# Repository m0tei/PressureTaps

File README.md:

# Pressure Taps

A 16-channel aero pressure tap board for ArtTU. It reads 16 pressure ports and one reference port over SPI and sends the data out on CAN. The sensors sit in sealed chambers, with a glued cover on top and a tube block underneath.

| | |
|---|---|
| Board size | 86 × 50 mm, 1.6 mm thick, 4 layers |
| Layers | Top, GND plane, GND+PWR (3V3) plane, bottom |
| MCU | STM32G483RET6 |
| Sensors | 17 × LPS27HHW (16 taps and 1 reference) on one SPI bus |
| Supply | 12 V in, 5 V and 3.3 V on board |
| Bus | CAN through a TJA1441, with switchable termination on P3 and P4 |
| Connector | TE Ampseal 2489696-1, 8 pin |
| Design tool | KiCad 10 |

> **Status:** this design passes KiCad's electrical and layout checks. This repository has no test results from a built board.

## The board

**Top side:** sensors on the left, MCU in the middle, CAN below it and the two regulators stacked in the top right corner. SWD, reset and BOOT0 are in a row along the top edge.

**Bottom side:** tube port labels and the Ampseal connector.

The sensor grid is centred top to bottom: 7.0 mm from the grid to each long edge. The clamp holes H5 to H8 are centred on the same line.

## Schematic

The full schematic is in [docs/schematic.pdf](docs/schematic.pdf). It has five sheets:

| Sheet | Contents |
|---|---|
| MCU | U1, BOOT0, reset, clock, SPI series resistors, MCU power and the VDDA regulator |
| Communication | CAN transceiver, choke, termination and ESD protection |
| Connectors | SWD header, Ampseal connector, mounting holes and fiducials |
| Power | 5 V and 3.3 V regulators, power flags |
| Sensors | The 17 pressure sensors and bulk capacitor |

The schematic style and part choices follow the ArtTU Gateway boards. Footprints named `GW_*` use pads measured from CAN_Gateway RevA.

## Ampseal pinout

| Pin | Signal |
|---|---|
| 1 to 4 | Not connected |
| 5 | GND |
| 6 | 12 V |
| 7 | CAN_N |
| 8 | CAN_P |

## Enclosure

The press-fit enclosure is in [mechanical/press_fit](mechanical/press_fit). It has four printed parts: case top, case bottom, sensor cover and tube block. STEP and STL files are in that folder.

To rebuild the parts, run this from the repository root:

```bash
uv run --no-project --python 3.12 --with cadquery==2.8.0 python -I mechanical/press_fit/enclosure.py mechanical/press_fit
```

The board size and hole positions in `enclosure.py` must match the PCB. Change both together.

## Bill of materials

The BOM is in [PressureTaps_BOM.csv](PressureTaps_BOM.csv). Parts shared with the Gateway use the same part numbers, manufacturers and suppliers.

## Open items

- R20 and R21 (33 Ω, SPI series resistors) have no part number yet.
- The P2, P3 and P4 pin headers do not fit under the case lid.
- D1 uses a standard SOT-323 footprint. The Gateway footprint for the same part has wider pad spacing, so it was not copied. Check it against the datasheet drawing.

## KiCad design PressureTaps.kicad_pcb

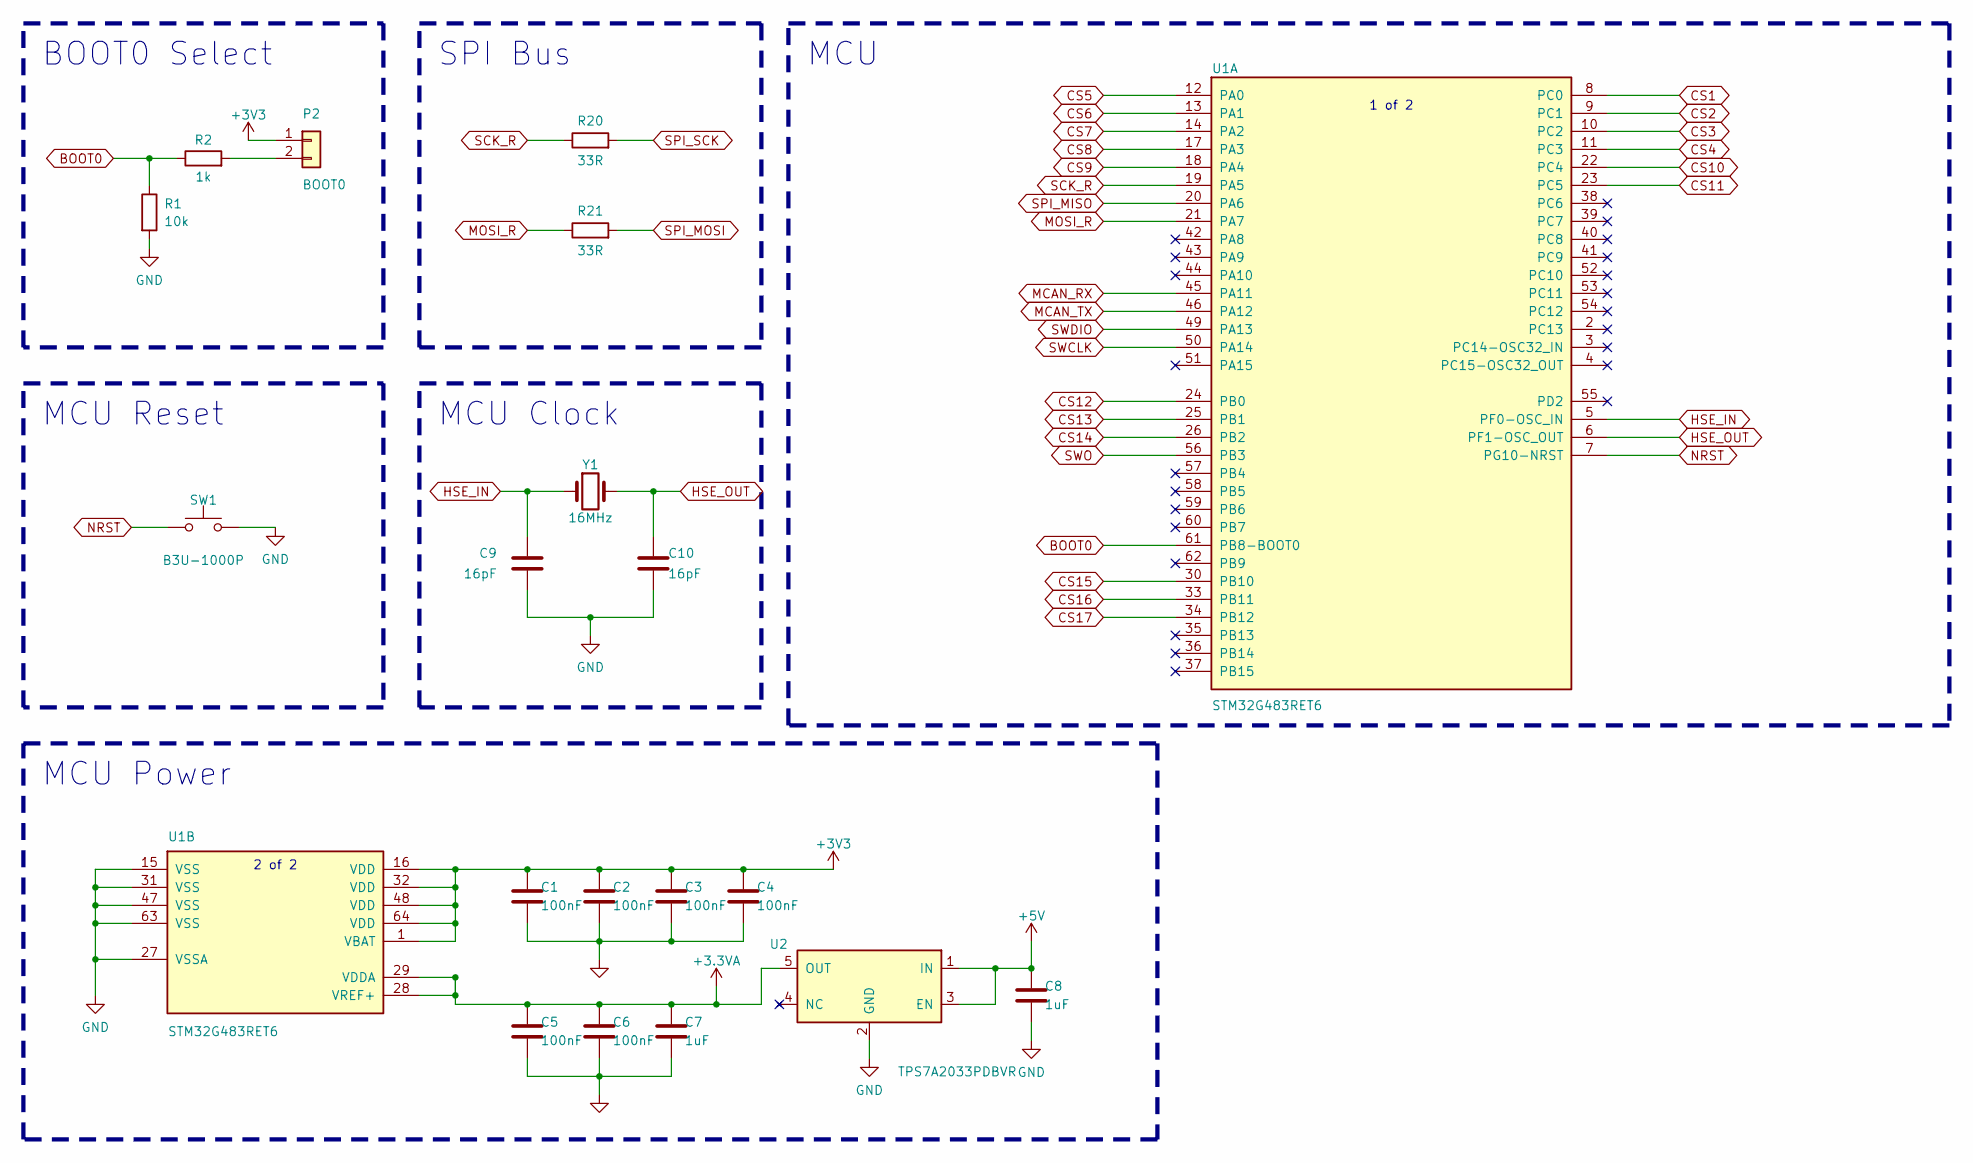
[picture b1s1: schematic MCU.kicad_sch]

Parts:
C1, C2, C3, C4, C5, C6: 100nF; GW_C1; MPN CC0603JRX7R9BB104
C7, C8: 1uF; GW_C7; MPN CC0603KRX5R8BB105
C9, C10: 16pF; GW_C9; MPN C0603C160J5HACTU
P2: BOOT0; GW_P2; MPN 62000211121
R1: 10k; GW_R1; MPN AF0603FR-0710KL
R2: 1k; GW_R2; MPN ERJ-6ENF1001V
R20, R21: 33R; GW_R1
SW1: B3U-1000P; SW_SPST_B3U-1000P; MPN B3U-1000P
U1: STM32G483RET6; GW_U1; MPN STM32G483RET6
U2: TPS7A2033PDBVR; GW_U2; MPN TPS7A2033PDBVR
Y1: 16MHz; GW_Y1; MPN ABM3-16.000MHZ-D2Y-T

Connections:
+3.3VA: C5.1, C6.1, C7.1, U1.28 (VREF+), U1.29 (VDDA), U2.5 (OUT)
+3V3: C1.1, C2.1, C3.1, C4.1, P2.1, U1.1 (VBAT), U1.16 (VDD), U1.32 (VDD), U1.48 (VDD), U1.64 (VDD); also elsewhere on the board
+5V: C8.1, U2.1 (IN), U2.3 (EN); also elsewhere on the board
BOOT0: R1.1, R2.1, U1.61 (PB8-BOOT0)
CS1: U1.8 (PC0); also elsewhere on the board
CS2: U1.9 (PC1); also elsewhere on the board
CS3: U1.10 (PC2); also elsewhere on the board
CS4: U1.11 (PC3); also elsewhere on the board
CS5: U1.12 (PA0); also elsewhere on the board
CS6: U1.13 (PA1); also elsewhere on the board
CS7: U1.14 (PA2); also elsewhere on the board
CS8: U1.17 (PA3); also elsewhere on the board
CS9: U1.18 (PA4); also elsewhere on the board
CS10: U1.22 (PC4); also elsewhere on the board
CS11: U1.23 (PC5); also elsewhere on the board
CS12: U1.24 (PB0); also elsewhere on the board
CS13: U1.25 (PB1); also elsewhere on the board
CS14: U1.26 (PB2); also elsewhere on the board
CS15: U1.30 (PB10); also elsewhere on the board
CS16: U1.33 (PB11); also elsewhere on the board
CS17: U1.34 (PB12); also elsewhere on the board
GND: C1.2, C2.2, C3.2, C4.2, C5.2, C6.2, C7.2, C8.2, C9.2, C10.2, R1.2, SW1.2, U1.15 (VSS), U1.27 (VSSA), U1.31 (VSS), U1.47 (VSS), U1.63 (VSS), U2.2 (GND); also elsewhere on the board
HSE_IN: C9.1, U1.5 (PF0-OSC_IN), Y1.1
HSE_OUT: C10.1, U1.6 (PF1-OSC_OUT), Y1.2
MCAN_RX: U1.45 (PA11); also elsewhere on the board
MCAN_TX: U1.46 (PA12); also elsewhere on the board
MOSI_R: R21.1, U1.21 (PA7)
NRST: SW1.1, U1.7 (PG10-NRST); also elsewhere on the board
unnamed: P2.2, R2.2
SCK_R: R20.1, U1.19 (PA5)
SPI_MISO: U1.20 (PA6); also elsewhere on the board
SPI_MOSI: R21.2; also elsewhere on the board
SPI_SCK: R20.2; also elsewhere on the board
SWCLK: U1.50 (PA14); also elsewhere on the board
SWDIO: U1.49 (PA13); also elsewhere on the board
SWO: U1.56 (PB3); also elsewhere on the board

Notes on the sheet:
BOOT0 Select
SPI Bus
MCU Reset
MCU Clock
MCU
1 of 2
MCU Power
2 of 2

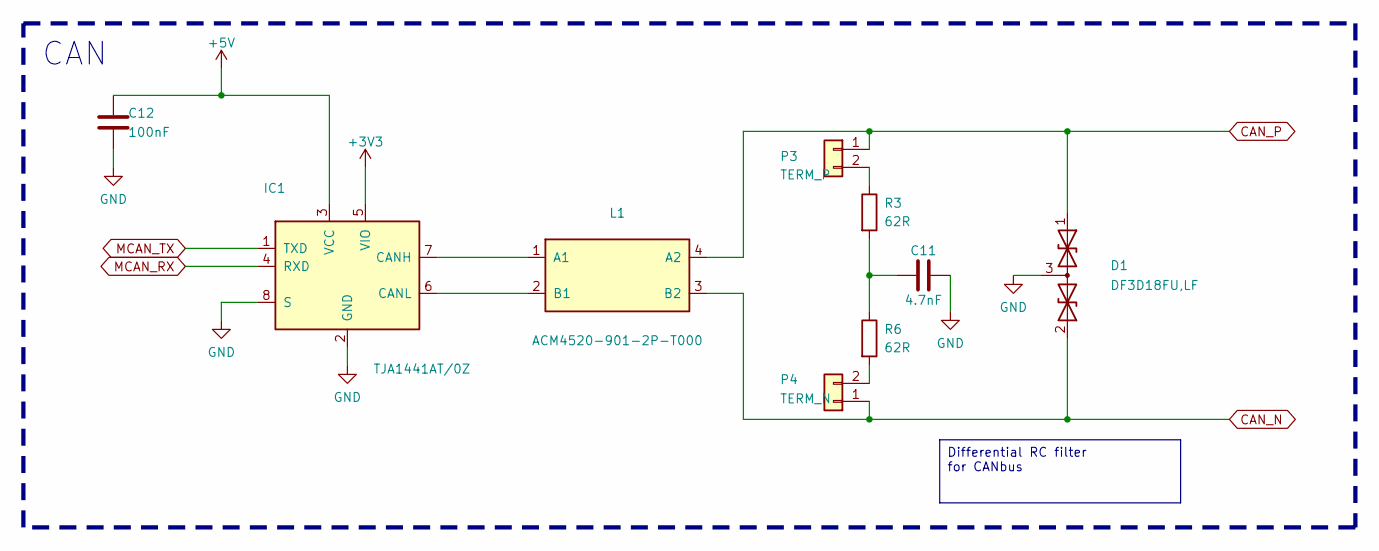
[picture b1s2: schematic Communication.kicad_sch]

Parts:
C11: 4.7nF; GW_C11; MPN C0603C472J5RACTU
C12: 100nF; GW_C12; MPN CC0603JRX7R9BB104
D1: DF3D18FU,LF; SOT-323_SC-70; MPN DF3D18FU,LF
IC1: TJA1441AT/0Z; GW_IC1; MPN TJA1441AT/0Z
L1: ACM4520-901-2P-T000; L_ACM4520; MPN ACM4520-901-2P-T000
P3: TERM_P; GW_P2; MPN 62000211121
P4: TERM_N; GW_P2; MPN 62000211121
R3, R6: 62R; GW_R3; MPN ERA3AEB620V

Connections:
+3V3: IC1.5 (VIO); also elsewhere on the board
+5V: C12.1, IC1.3 (VCC); also elsewhere on the board
CAN_N: D1.2 (A2), L1.3 (B2), P4.1; also elsewhere on the board
CAN_P: D1.1 (A1), L1.4 (A2), P3.1; also elsewhere on the board
GND: C11.2, C12.2, D1.3 (common), IC1.2 (GND), IC1.8 (S); also elsewhere on the board
MCAN_RX: IC1.4 (RXD); also elsewhere on the board
MCAN_TX: IC1.1 (TXD); also elsewhere on the board
unnamed: C11.1, R3.2, R6.1
unnamed: IC1.7 (CANH), L1.1 (A1)
unnamed: IC1.6 (CANL), L1.2 (B1)
unnamed: P3.2, R3.1
unnamed: P4.2, R6.2

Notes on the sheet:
CAN
Differential RC filter for CANbus

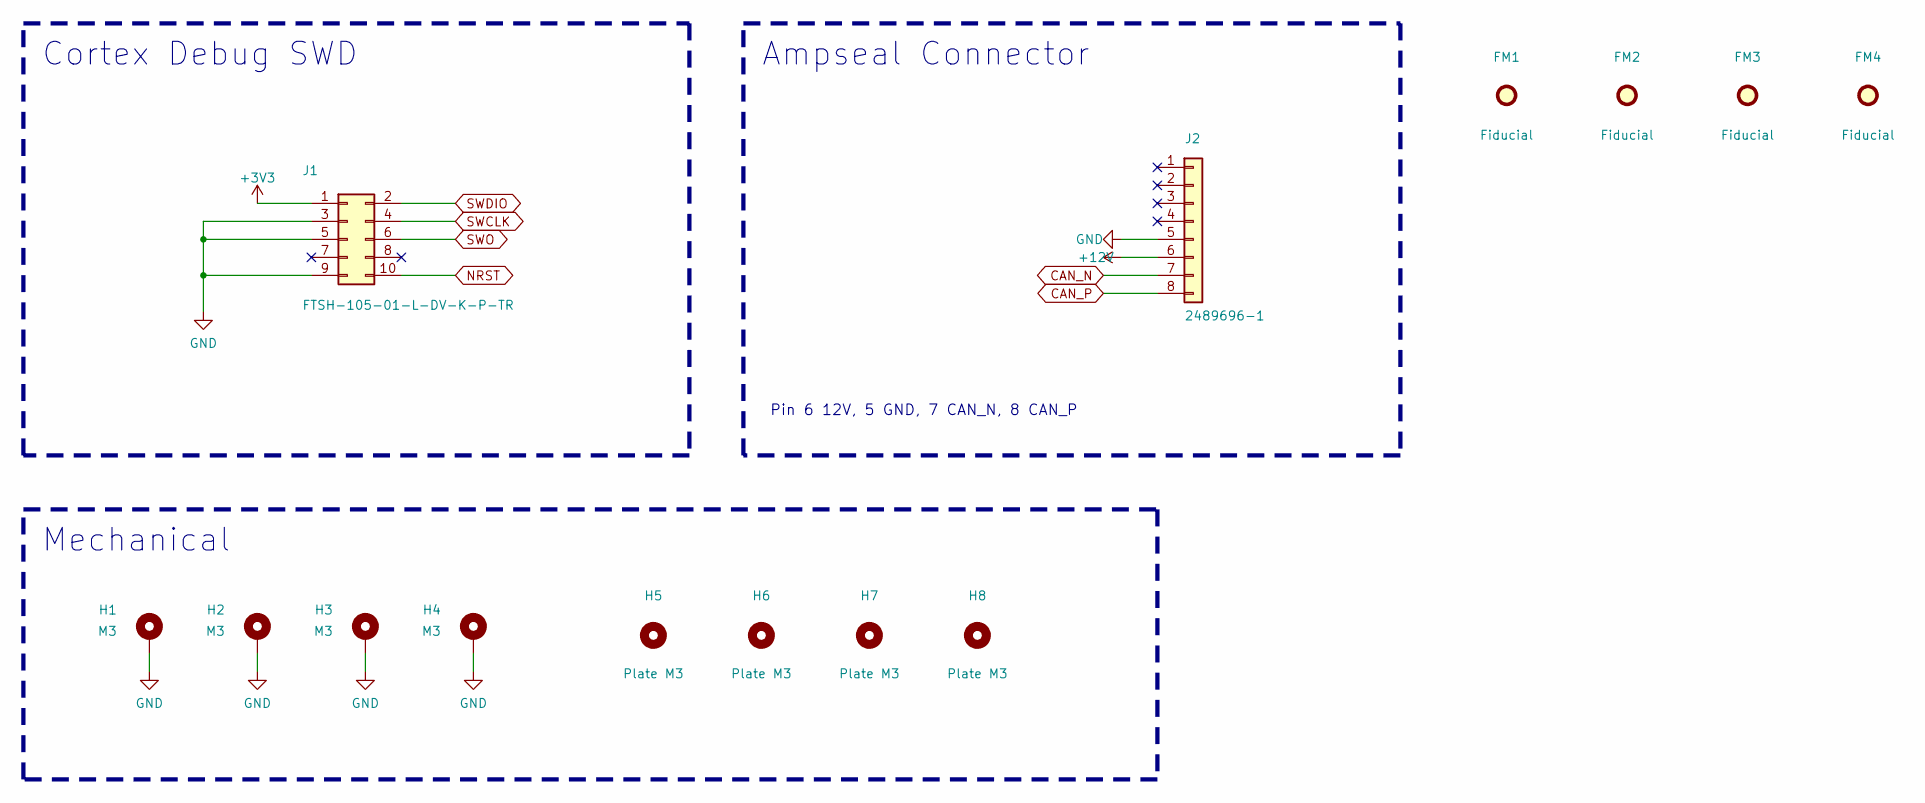
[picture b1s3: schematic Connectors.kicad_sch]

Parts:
FM1, FM2, FM3, FM4: Fiducial; Fiducial_1mm_Mask2mm
H1, H2, H3, H4: M3; MountingHole_3.2mm_M3_Pad
H5, H6, H7, H8: Plate M3; MountingHole_3.2mm_M3
J1: FTSH-105-01-L-DV-K-P-TR; GW_J1; MPN FTSH-105-01-L-DV-K-P-TR
J2: 2489696-1; Ampseal_8P_90deg; MPN 2489696-1

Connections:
+3V3: J1.1; also elsewhere on the board
+12V: J2.6; also elsewhere on the board
CAN_N: J2.7; also elsewhere on the board
CAN_P: J2.8; also elsewhere on the board
GND: H1.1, H2.1, H3.1, H4.1, J1.3, J1.5, J1.9, J2.5; also elsewhere on the board
NRST: J1.10; also elsewhere on the board
SWCLK: J1.4; also elsewhere on the board
SWDIO: J1.2; also elsewhere on the board
SWO: J1.6; also elsewhere on the board

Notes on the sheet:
Cortex Debug SWD
Ampseal Connector
Pin 6 12V, 5 GND, 7 CAN_N, 8 CAN_P
Mechanical

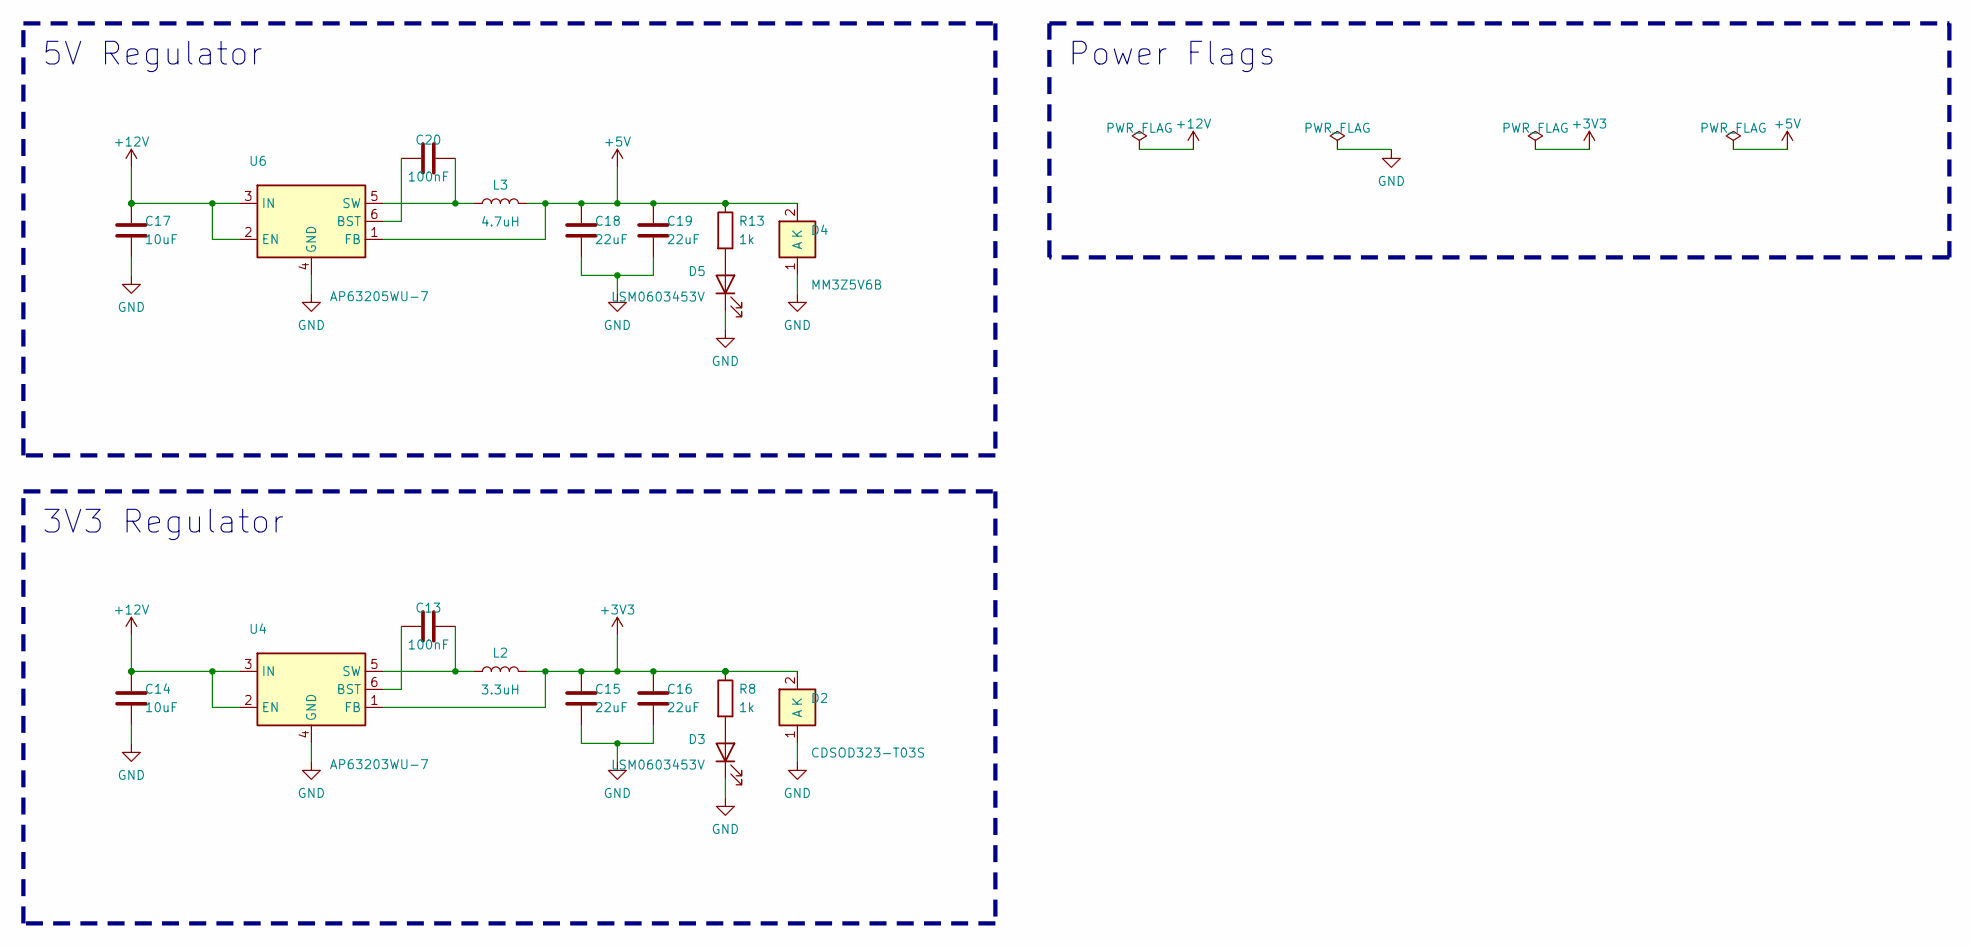
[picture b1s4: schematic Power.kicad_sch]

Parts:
C13, C20: 100nF; GW_C7; MPN CC0603KRX7R8BB104
C14, C17: 10uF; GW_C14; MPN CL21A106KAYNNNE
C15, C16, C18, C19: 22uF; GW_C15; MPN GRM188R61A226ME15D
D2: CDSOD323-T03S; GW_D2; MPN CDSOD323-T03S
D3, D5: LSM0603453V; GW_D3; MPN LSM0603453V
D4: MM3Z5V6B; GW_D4; MPN MM3Z5V6B
L2: 3.3uH; GW_L2; MPN DFE252012P-3R3M=P2
L3: 4.7uH; GW_L3; MPN DFE252012F-4R7M=P2
R8, R13: 1k; GW_R8; MPN ERJ-6ENF1001V
U4: AP63203WU-7; GW_U4; MPN AP63203WU-7
U6: AP63205WU-7; GW_U4; MPN AP63205WU-7

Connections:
+3V3: C15.1, C16.1, D2.2 (K), L2.2, R8.1, U4.1 (FB); also elsewhere on the board
+5V: C18.1, C19.1, D4.2 (K), L3.2, R13.1, U6.1 (FB); also elsewhere on the board
+12V: C14.1, C17.1, U4.2 (EN), U4.3 (IN), U6.2 (EN), U6.3 (IN); also elsewhere on the board
GND: C14.2, C15.2, C16.2, C17.2, C18.2, C19.2, D2.1 (A), D3.1 (K), D4.1 (A), D5.1 (K), U4.4 (GND), U6.4 (GND); also elsewhere on the board
unnamed: D3.2 (A), R8.2
unnamed: D5.2 (A), R13.2
unnamed: C13.1, U4.6 (BST)
unnamed: C13.2, L2.1, U4.5 (SW)
unnamed: C20.1, U6.6 (BST)
unnamed: C20.2, L3.1, U6.5 (SW)

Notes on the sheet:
5V Regulator
3V3 Regulator
Power Flags

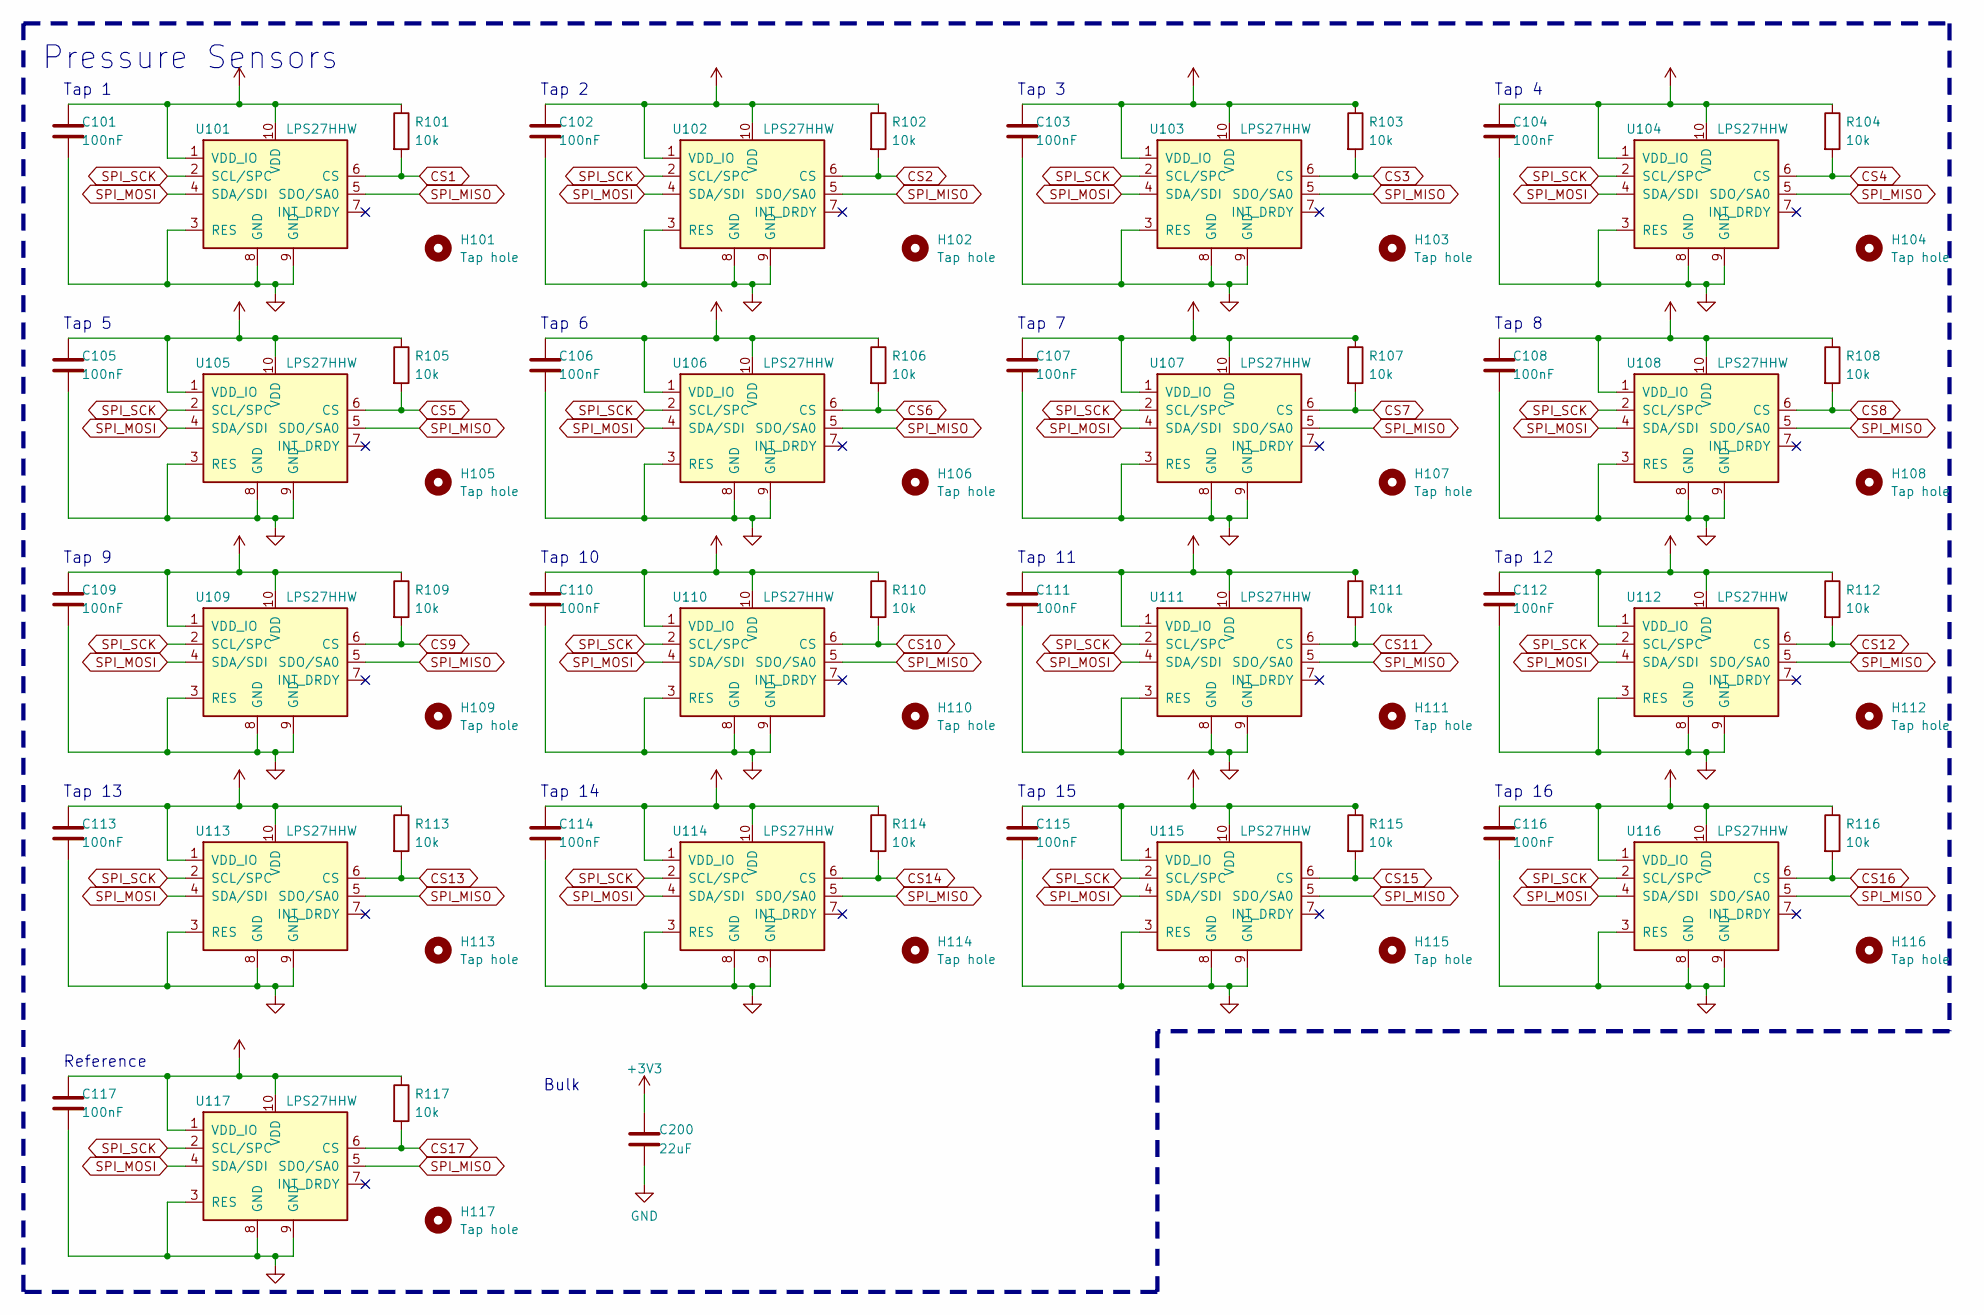
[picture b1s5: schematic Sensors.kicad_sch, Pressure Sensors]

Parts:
C101, C102, C103, C104, C105, C106, C107, C108, C109, C110, C111, C112, C113, C114, C115, C116, C117: 100nF; GW_C1; MPN CC0603JRX7R9BB104
C200: 22uF; GW_C15; MPN GRM188R61A226ME15D
H101, H102, H103, H104, H105, H106, H107, H108, H109, H110, H111, H112, H113, H114, H115, H116, H117: Tap hole; TapHole_1.5mm
R101, R102, R103, R104, R105, R106, R107, R108, R109, R110, R111, R112, R113, R114, R115, R116, R117: 10k; GW_R1; MPN AF0603FR-0710KL
U101, U102, U103, U104, U105, U106, U107, U108, U109, U110, U111, U112, U113, U114, U115, U116, U117: LPS27HHW; MPN LPS27HHWTR

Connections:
+3V3: C101.1, C102.1, C103.1, C104.1, C105.1, C106.1, C107.1, C108.1, C109.1, C110.1, C111.1, C112.1, C113.1, C114.1, C115.1, C116.1, C117.1, C200.1, R101.1, R102.1, R103.1, R104.1, R105.1, R106.1, R107.1, R108.1, R109.1, R110.1, R111.1, R112.1, R113.1, R114.1, R115.1, R116.1, R117.1, U101.1 (VDD_IO), U101.10 (VDD), U102.1 (VDD_IO), U102.10 (VDD), U103.1 (VDD_IO), U103.10 (VDD), U104.1 (VDD_IO), U104.10 (VDD), U105.1 (VDD_IO), U105.10 (VDD), U106.1 (VDD_IO), U106.10 (VDD), U107.1 (VDD_IO), U107.10 (VDD), U108.1 (VDD_IO), U108.10 (VDD), U109.1 (VDD_IO), U109.10 (VDD), U110.1 (VDD_IO), U110.10 (VDD), U111.1 (VDD_IO), U111.10 (VDD), U112.1 (VDD_IO), U112.10 (VDD), U113.1 (VDD_IO), U113.10 (VDD), U114.1 (VDD_IO), U114.10 (VDD), U115.1 (VDD_IO), U115.10 (VDD), U116.1 (VDD_IO), U116.10 (VDD), U117.1 (VDD_IO), U117.10 (VDD); also elsewhere on the board
CS1: R101.2, U101.6 (CS); also elsewhere on the board
CS2: R102.2, U102.6 (CS); also elsewhere on the board
CS3: R103.2, U103.6 (CS); also elsewhere on the board
CS4: R104.2, U104.6 (CS); also elsewhere on the board
CS5: R105.2, U105.6 (CS); also elsewhere on the board
CS6: R106.2, U106.6 (CS); also elsewhere on the board
CS7: R107.2, U107.6 (CS); also elsewhere on the board
CS8: R108.2, U108.6 (CS); also elsewhere on the board
CS9: R109.2, U109.6 (CS); also elsewhere on the board
CS10: R110.2, U110.6 (CS); also elsewhere on the board
CS11: R111.2, U111.6 (CS); also elsewhere on the board
CS12: R112.2, U112.6 (CS); also elsewhere on the board
CS13: R113.2, U113.6 (CS); also elsewhere on the board
CS14: R114.2, U114.6 (CS); also elsewhere on the board
CS15: R115.2, U115.6 (CS); also elsewhere on the board
CS16: R116.2, U116.6 (CS); also elsewhere on the board
CS17: R117.2, U117.6 (CS); also elsewhere on the board
GND: C101.2, C102.2, C103.2, C104.2, C105.2, C106.2, C107.2, C108.2, C109.2, C110.2, C111.2, C112.2, C113.2, C114.2, C115.2, C116.2, C117.2, C200.2, U101.3 (RES), U101.8 (GND), U101.9 (GND), U102.3 (RES), U102.8 (GND), U102.9 (GND), U103.3 (RES), U103.8 (GND), U103.9 (GND), U104.3 (RES), U104.8 (GND), U104.9 (GND), U105.3 (RES), U105.8 (GND), U105.9 (GND), U106.3 (RES), U106.8 (GND), U106.9 (GND), U107.3 (RES), U107.8 (GND), U107.9 (GND), U108.3 (RES), U108.8 (GND), U108.9 (GND), U109.3 (RES), U109.8 (GND), U109.9 (GND), U110.3 (RES), U110.8 (GND), U110.9 (GND), U111.3 (RES), U111.8 (GND), U111.9 (GND), U112.3 (RES), U112.8 (GND), U112.9 (GND), U113.3 (RES), U113.8 (GND), U113.9 (GND), U114.3 (RES), U114.8 (GND), U114.9 (GND), U115.3 (RES), U115.8 (GND), U115.9 (GND), U116.3 (RES), U116.8 (GND), U116.9 (GND), U117.3 (RES), U117.8 (GND), U117.9 (GND); also elsewhere on the board
SPI_MISO: U101.5 (SDO/SA0), U102.5 (SDO/SA0), U103.5 (SDO/SA0), U104.5 (SDO/SA0), U105.5 (SDO/SA0), U106.5 (SDO/SA0), U107.5 (SDO/SA0), U108.5 (SDO/SA0), U109.5 (SDO/SA0), U110.5 (SDO/SA0), U111.5 (SDO/SA0), U112.5 (SDO/SA0), U113.5 (SDO/SA0), U114.5 (SDO/SA0), U115.5 (SDO/SA0), U116.5 (SDO/SA0), U117.5 (SDO/SA0); also elsewhere on the board
SPI_MOSI: U101.4 (SDA/SDI), U102.4 (SDA/SDI), U103.4 (SDA/SDI), U104.4 (SDA/SDI), U105.4 (SDA/SDI), U106.4 (SDA/SDI), U107.4 (SDA/SDI), U108.4 (SDA/SDI), U109.4 (SDA/SDI), U110.4 (SDA/SDI), U111.4 (SDA/SDI), U112.4 (SDA/SDI), U113.4 (SDA/SDI), U114.4 (SDA/SDI), U115.4 (SDA/SDI), U116.4 (SDA/SDI), U117.4 (SDA/SDI); also elsewhere on the board
SPI_SCK: U101.2 (SCL/SPC), U102.2 (SCL/SPC), U103.2 (SCL/SPC), U104.2 (SCL/SPC), U105.2 (SCL/SPC), U106.2 (SCL/SPC), U107.2 (SCL/SPC), U108.2 (SCL/SPC), U109.2 (SCL/SPC), U110.2 (SCL/SPC), U111.2 (SCL/SPC), U112.2 (SCL/SPC), U113.2 (SCL/SPC), U114.2 (SCL/SPC), U115.2 (SCL/SPC), U116.2 (SCL/SPC), U117.2 (SCL/SPC); also elsewhere on the board

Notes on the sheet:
Pressure Sensors
Tap 1
Tap 2
Tap 3
Tap 4
Tap 5
Tap 6
Tap 7
Tap 8
Tap 9
Tap 10
Tap 11
Tap 12
Tap 13
Tap 14
Tap 15
Tap 16
Reference
Bulk

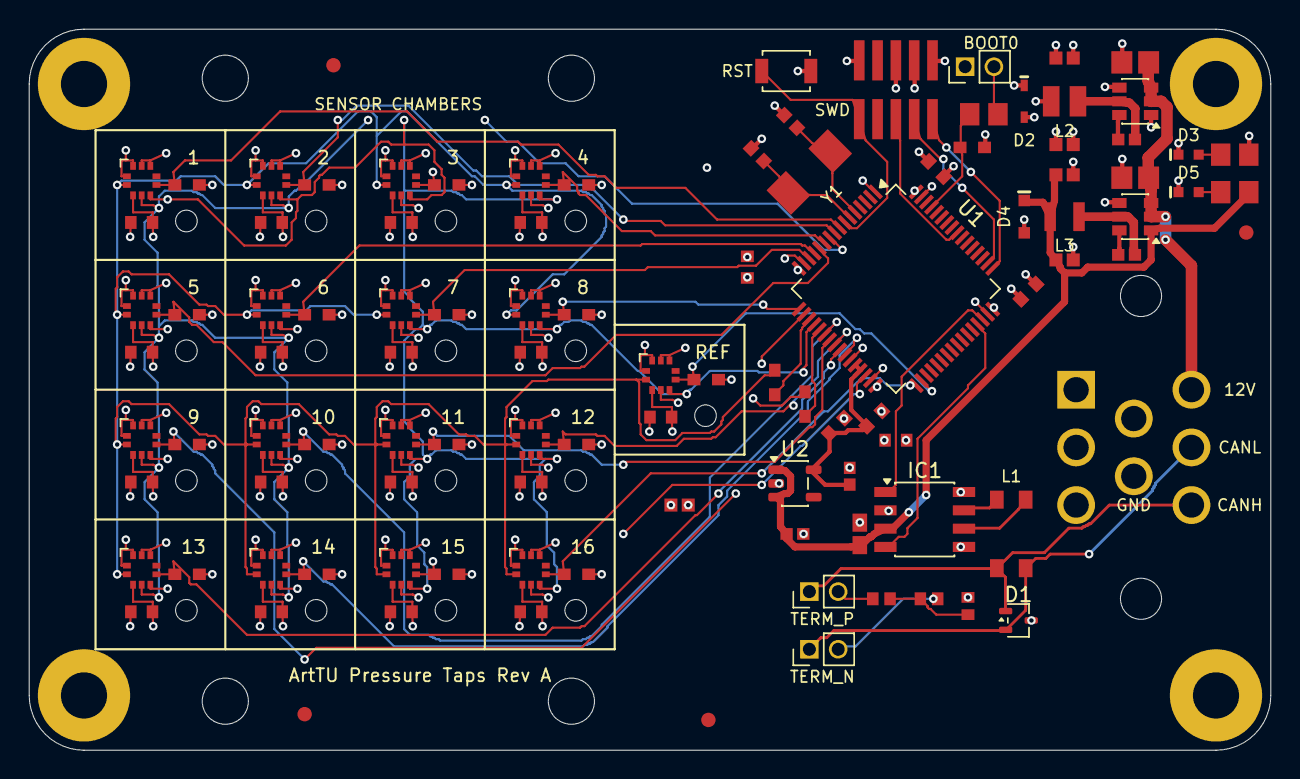
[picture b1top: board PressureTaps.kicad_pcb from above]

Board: 4 copper layers, 86.1 x 50.0 mm, 129 parts (1 on the bottom side), 50 nets.

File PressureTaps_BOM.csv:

"Reference","Value","Footprint","MPN","Manufacturer","Supplier","Supplier PN","Qty"
"C1-C6,C101-C117","100nF","PressureTaps:GW_C1","CC0603JRX7R9BB104","Yageo Group","Mouser","603-CC603JRX7R9BB104","23"
"C7,C8","1uF","PressureTaps:GW_C7","CC0603KRX5R8BB105","Yageo Group","Mouser","603-CC603KRX5R8BB105","2"
"C9,C10","16pF","PressureTaps:GW_C9","C0603C160J5HACTU","Yageo Group","Mouser","80-C0603C160J5HACTU","2"
"C11","4.7nF","PressureTaps:GW_C11","C0603C472J5RACTU","Yageo Group","DigiKey","399-C0603C472J5RACTUDKR-ND","1"
"C12","100nF","PressureTaps:GW_C12","CC0603JRX7R9BB104","Yageo Group","Mouser","603-CC603JRX7R9BB104","1"
"C13,C20","100nF","PressureTaps:GW_C7","CC0603KRX7R8BB104","Yageo Group","Mouser","603-CC603KRX7R8BB104","2"
"C14,C17","10uF","PressureTaps:GW_C14","CL21A106KAYNNNE","Samsung Electro-Mechanics","","","2"
"C15,C16,C18,C19,C200","22uF","PressureTaps:GW_C15","GRM188R61A226ME15D","Murata","","","5"
"D1","DF3D18FU,LF","Package_TO_SOT_SMD:SOT-323_SC-70","DF3D18FU,LF","Toshiba","Mouser","757-DF3D18FULF","1"
"D2","CDSOD323-T03S","PressureTaps:GW_D2","CDSOD323-T03S","Bourns","Mouser","652-CDSOD323-T03S","1"
"D3,D5","LSM0603453V","PressureTaps:GW_D3","LSM0603453V","VCC","DigiKey","LSM0603453VCT-ND","2"
"D4","MM3Z5V6B","PressureTaps:GW_D4","MM3Z5V6B","onsemi","DigiKey","MM3Z5V6BDKR-ND","1"
"FM1-FM4","Fiducial","Fiducial:Fiducial_1mm_Mask2mm","","","","","4"
"H1-H4","M3","MountingHole:MountingHole_3.2mm_M3_Pad","","","","","4"
"H5-H8","Plate M3","MountingHole:MountingHole_3.2mm_M3","","","","","4"
"H101-H117","Tap hole","PressureTaps:TapHole_1.5mm","","","","","17"
"IC1","TJA1441AT/0Z","PressureTaps:GW_IC1","TJA1441AT/0Z","","","","1"
"J1","FTSH-105-01-L-DV-K-P-TR","PressureTaps:GW_J1","FTSH-105-01-L-DV-K-P-TR","Samtec","Mouser","200-FTSH10501LDVKPTR","1"
"J2","2489696-1","PressureTaps:Ampseal_8P_90deg","2489696-1","","","","1"
"L1","ACM4520-901-2P-T000","PressureTaps:L_ACM4520","ACM4520-901-2P-T000","TDK","Mouser","810-ACM45209012PT000","1"
"L2","3.3uH","PressureTaps:GW_L2","DFE252012P-3R3M=P2","Murata","DigiKey","490-10650-6-ND","1"
"L3","4.7uH","PressureTaps:GW_L3","DFE252012F-4R7M=P2","Murata","DigiKey","490-13051-1-ND","1"
"P2","BOOT0","PressureTaps:GW_P2","62000211121","Wurth Elektronik","","","1"
"P3","TERM_P","PressureTaps:GW_P2","62000211121","Wurth Elektronik","","","1"
"P4","TERM_N","PressureTaps:GW_P2","62000211121","Wurth Elektronik","","","1"
"R1,R101-R117","10k","PressureTaps:GW_R1","AF0603FR-0710KL","Yageo Group","Mouser","603-AF0603FR-0710KL","18"
"R2","1k","PressureTaps:GW_R2","ERJ-6ENF1001V","Panasonic","","","1"
"R3,R6","62R","PressureTaps:GW_R3","ERA3AEB620V","Panasonic","DigiKey","P62DBCT-ND","2"
"R8,R13","1k","PressureTaps:GW_R8","ERJ-6ENF1001V","Panasonic","","","2"
"R20,R21","33R","PressureTaps:GW_R1","","","","","2"
"SW1","B3U-1000P","Button_Switch_SMD:SW_SPST_B3U-1000P","B3U-1000P","","","","1"
"U1","STM32G483RET6","PressureTaps:GW_U1","STM32G483RET6","","","","1"
"U2","TPS7A2033PDBVR","PressureTaps:GW_U2","TPS7A2033PDBVR","Texas Instruments","Mouser","595-TPS7A2033PDBVR","1"
"U4","AP63203WU-7","PressureTaps:GW_U4","AP63203WU-7","Diodes Inc.","Mouser","621-AP63203WU-7","1"
"U6","AP63205WU-7","PressureTaps:GW_U4","AP63205WU-7","Diodes Inc.","","","1"
"U101-U117","LPS27HHW","PressureTaps:LPS27HHW","LPS27HHWTR","","","","17"
"Y1","16MHz","PressureTaps:GW_Y1","ABM3-16.000MHZ-D2Y-T","Abracon","Mouser","815-ABM3-16-D2Y-T","1"
